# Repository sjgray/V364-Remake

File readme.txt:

Commodore V364 Prototype Remake Project   Steve J. Gray
=======================================

This is a project to remake the V364 prototype computer from Commodore.
This would have been the flagship model in the TED/264 series, and
would feature a larger case with numeric keypad and built-in speech
synthesis using a more integrated version of the Magic Voice ("MV")
cartridge that was released for the C64.

This project will involve several different tasks:

 1) Create a PCB that matches the existing prototype layout as close as possible.
 2) Create a functional equivalent to the custom speech gate array chip.
 3) Create an MX switch compatible keyboard with numeric pad OR just the numeric
    pad that can be used with a standard Plus/4 keyboard.
 4) Create cherry MX keycaps.
 5) Create 3D modelled cursor arrow keys and function keys.
 6) Create a 3D modelled case of the V364 case to match the V364 motherboard
 7) Create a 3D modelled case that will accept a Plus/4 motherboard and keyboard
    for those just wanting the look. Use addon numeric keypad.
 8) Create a speech cartridge for existing 264-series computers.
 9) Create an internal Speech development board for 264-series.
10) Create replica case badge.
11) Clone the C64 MV to confirm schematics and as a base for other variations.

Status Overview  **** This project is not complete!!!! ****
---------------

The following have been posted even if not complete:

* 3D case for Plus/4 motherboard. In progress. Has not been printed.
* Complete "full" keyboard. Uses standard MX switches. Tested working. May need updating.
* Separate Numeric Pad. Supports standard and low-profile MX switches. Untested.
* Complete Custom Cherry MX keycaps. Tested ok.
* Preliminary Motherboard PCB. Most components are in place. No routing.
* C64 Magic Voice clone. Mostly done.

Keyboard
--------

A mechanical keyboard PCB has been produced with numeric pad. Custom cherry keycaps
were ordered from Maxkeyboard.com. These were tested on a real Plus/4 computer and
are working. A standalone MX numeric keypad PCB will be created for those wanting to
use a Plus/4 keyboard (feasibility to be determined).

Numeric Keypad
---------------

This has not been tested! Use at own risk. The original "full" V364 keyboard was
loaded and everything but the numeric pad and one connecter were retained so there
should be no reason the numpad would not work, however it may require modifications
depending on the final case design.

The V364 motherboard should have an extra keyboard connector to connect
both a Plus/4 keyboard and this numeric pad. For Plus/4 motherboards it
will need a 2-to-1 adapter board to connect both.

I have ordered PCBs and will build one with low-profile switches to confirm operation.

Keycaps
-------

Keycaps have been completed for the normal cherry type keys. The non-standard
function keys and arrow cursor keys have not been started. These will have to wait
for the 3D case to be completed.

Keycap Labels
-------------

 Custom colour printed keycaps were made by Maxkeyboard.com. A SVG file was submitted
in order to make the dyesub printed keycaps. This SVG file can also be used to make water-slide or vinyl sheet for using on blank keycaps.

Case
----

Initially I took 2 Plus/4 cases and modded them to resemble a V364 case. Of course
the function key area was wrong but it allowed me to test a Plus/4 motherboard and
the MX keyboard. The Plus/4 keyboard ribbon connector was replaced with a normal
pin header (like the C64) for testing.

A 3D replica case is being designed using the free version of Sketchup. It is mostly
complete but has not been printed. Final design will depend on the motherboard PCB
design to match port locations and mounting holes etc.

Badge
-----

I want to duplicate the real V364 badge. This was done in the same style as the Plus/4
badge. It uses raised silver logo, letters, and model# as well as the same multi-coloured
rainbow stripes. I think this will have to be done with separate printed components.
The base can be made of plastic with colour-laser printed sticker applied over top. The
rest will need to be resin-printed in order to get the proper detail and spray-painted
silver. Each will need to be glued on top of the sticker sheet. Currently only the silver
parts have been 3D modelled.

Motherboard PCB
---------------

A replica PCB is in progress using Kicad. The board dimensions and layout are mostly
done by underlaying a photo of a real V364 motherboard for alignment. The Plus/4 schematic was used as a base and the speech section was derived by work done by
Bo Zimmerman and Richard Atkinson. The Magic Voice schematic was used to obtain the
Toshiba T6721 chip pinout and audio output circuit.

Custom Gate Array
-----------------

This has not started. Since the V364 has been emulated it should be possible to
duplicate the functionality on some type of programmable logic chip and turned into
a pin-compatible plug-in board.

Speech Cartridge
----------------

This is a cartridge based on the V364 speech circuitry. It consists of just the speech chips
with an audio output jack. It will also need a connection to the "F0" pin on the PLA inside
the computer.

Speech Dev Board
-----------------

This is a development board to add speech internally using either the MV chipset or the
custom V364 Gate Array (recreated in FPGA etc). The MV circuit was simplified for the 264.
It connects via ribbon cable to one ROM socket on the computer motherboard and has several
flyouts to connect various places.

The ROM from the computer is transferred to this board. The V364 ROM/EPROM is installed in
the other socket and the Toshiba T6721A in it's socket.

* If you are using the MV set: install the 6525 and LA05 chips.
* If you have the V364 Gate Array recreation just install that only.

C64 Magic Voice replica
-----------------------

This is a replica of the C64 Magic Voice cartridge. This will verify that existing schematics
of the Magic Voice are correct and then we can use this as the basis for 264-series versions
if the custom gate array can not be cloned. The schematic was entered into Kicad and a board
was created, along with creating a Magic Voice gate array symbol. The design is mostly completed,
with layout and components closely matching the original except for a few minor changes to
some traces due to Kicad's trace constraints, and also the RCA connectors could not
be found so a modern version was substituted.

Project notes
-------------

I will release work-in-progress for anyone interested in following along. Anyone that
wishes to help is encouraged to contact me.

Steve

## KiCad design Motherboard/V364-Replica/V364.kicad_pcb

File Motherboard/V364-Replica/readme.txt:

Commodore V364 Prototype Remake Project   Steve J. Gray
=======================================

This is a project to remake the V364 prototype computer from Commodore.
This would have been the flagship model in the TED/264 series, and
would feature a larger case with numeric keypad and built-in speech
synthesis using a more integrated version of the Magic Voice cartridge
that was released for the C64.

Motherboard PCB
---------------

A replica PCB is in progress using Kicad. The board dimensions and layout are mostly
done by underlaying a photo of a real V364 motherboard for alignment. The Plus/4 schematic was used as a base and the speech section was derived by work done by
Bo Zimmerman and Richard Atkinson. The Magic Voice schematic was used to obtain the
Toshiba T6721 chip pinout and audio output circuit.

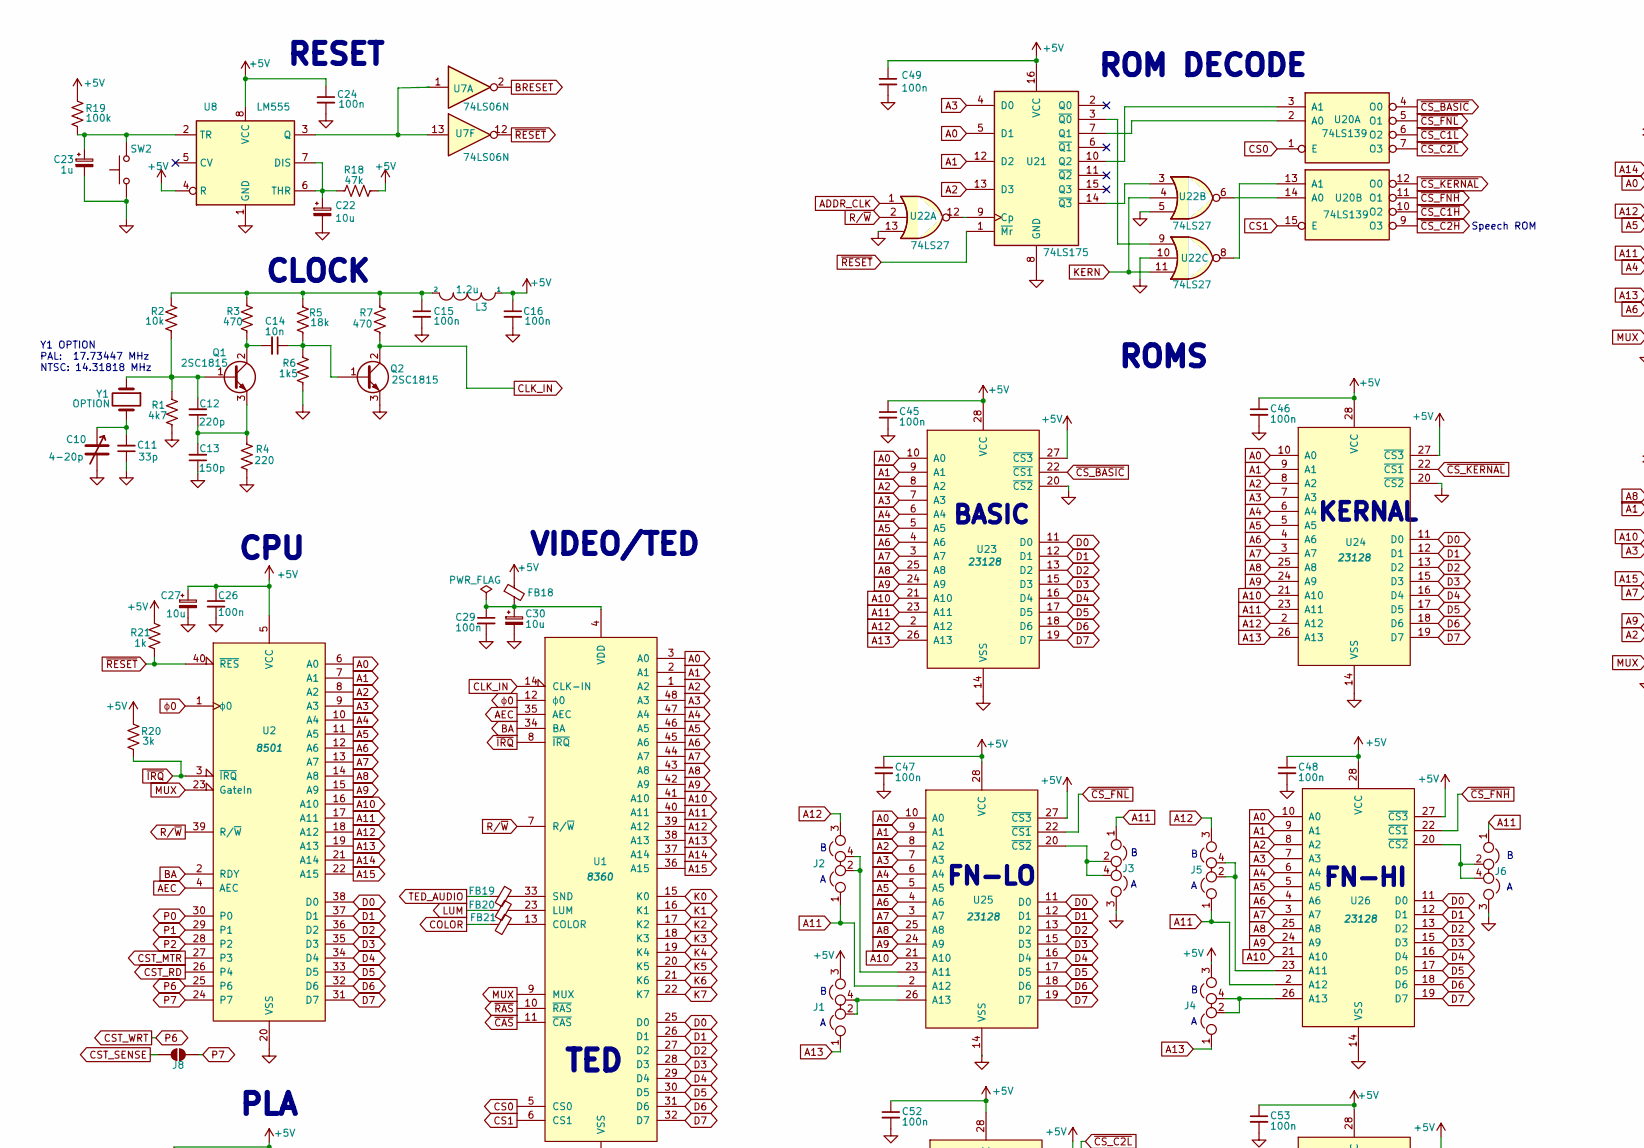
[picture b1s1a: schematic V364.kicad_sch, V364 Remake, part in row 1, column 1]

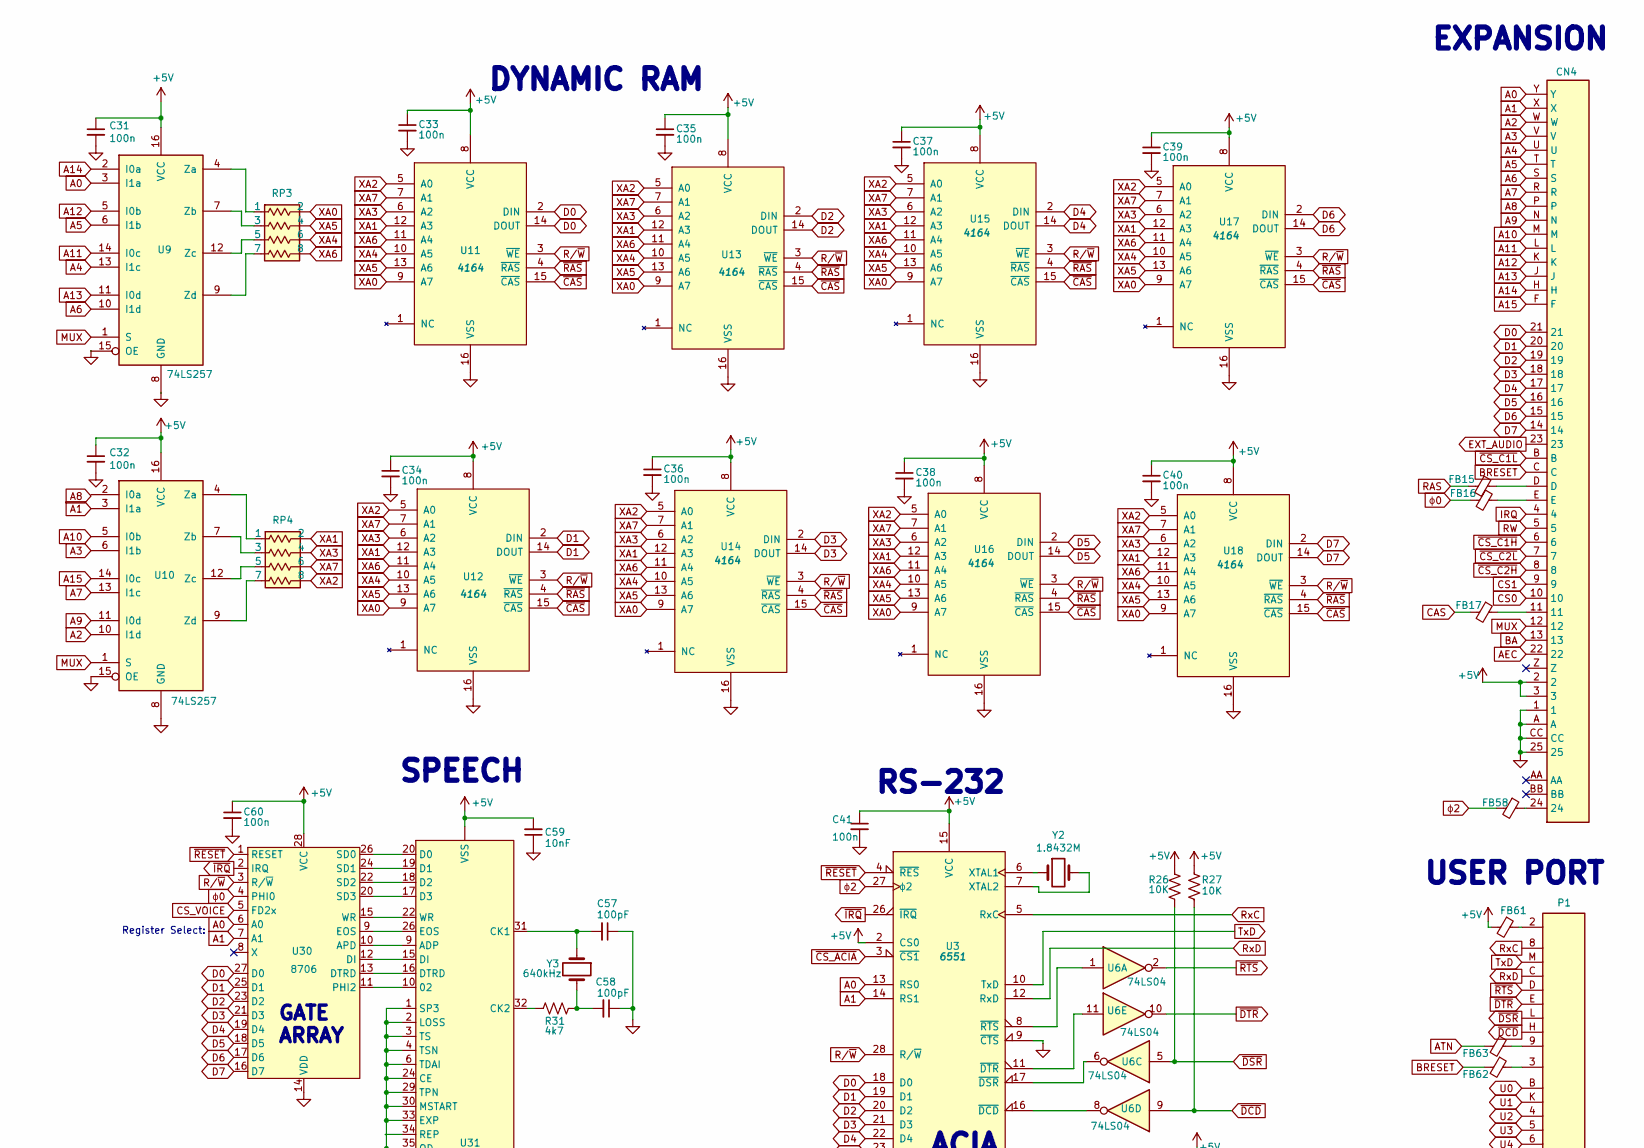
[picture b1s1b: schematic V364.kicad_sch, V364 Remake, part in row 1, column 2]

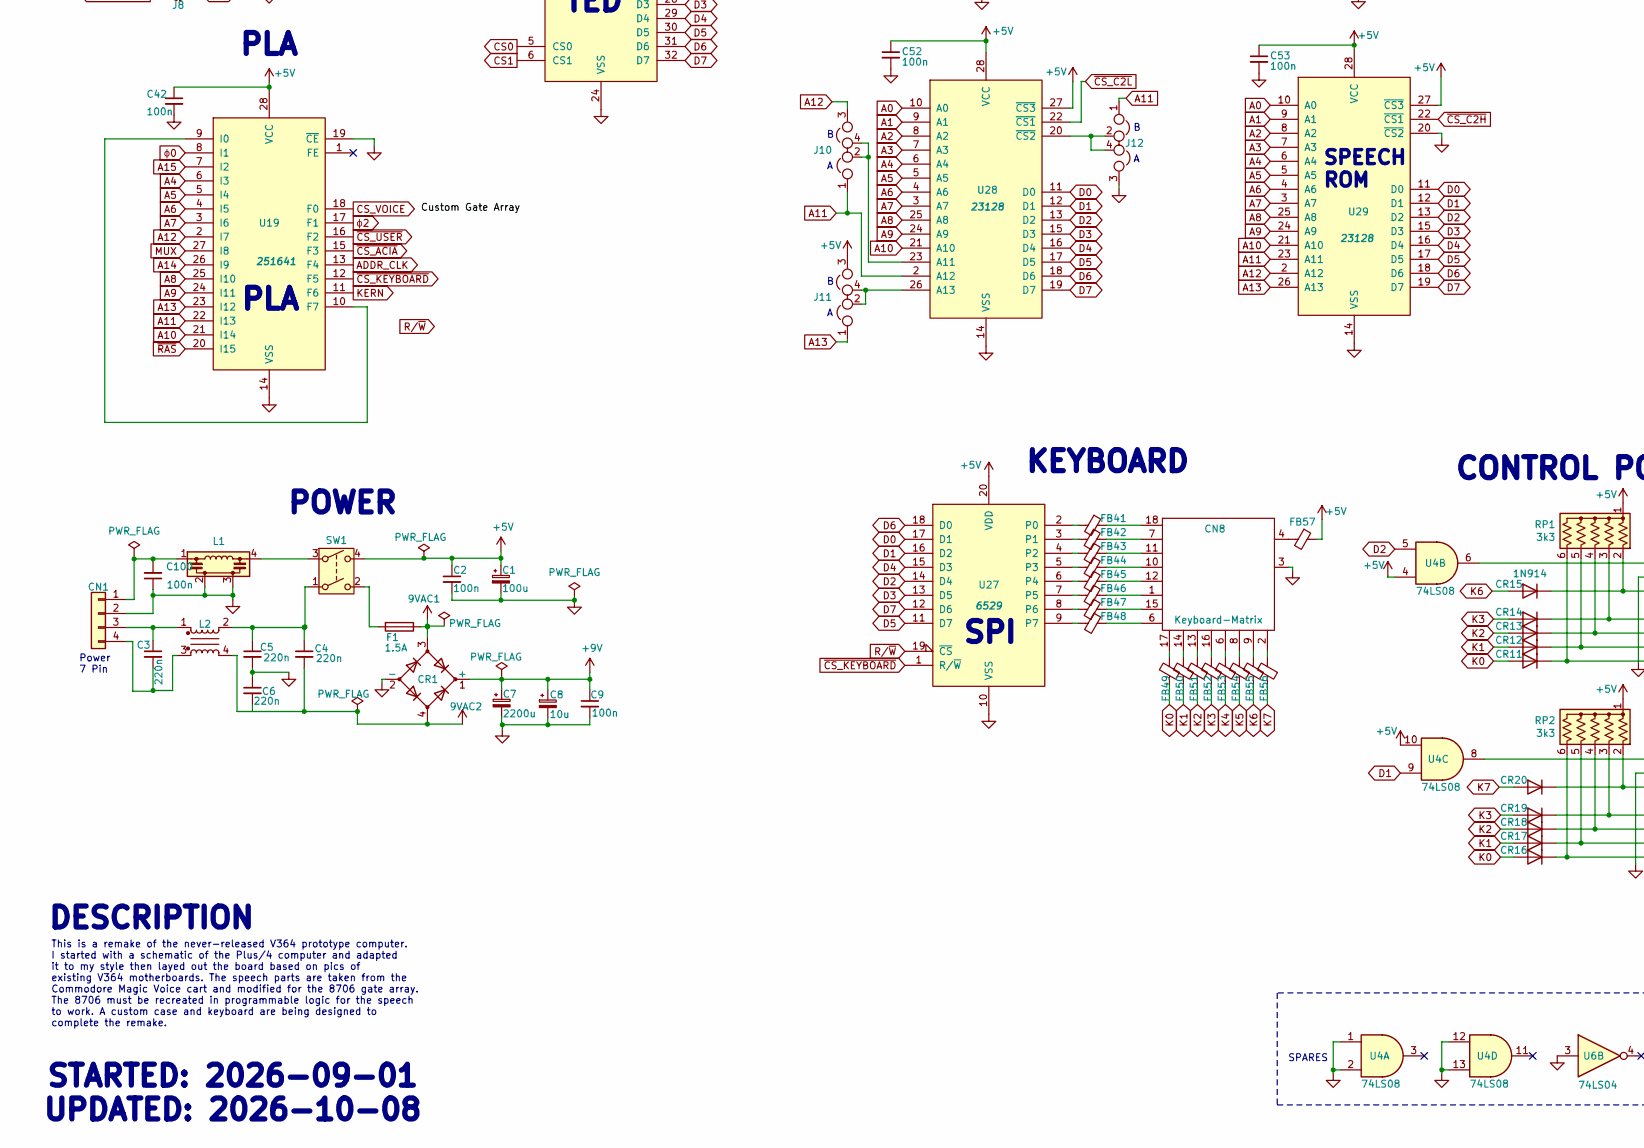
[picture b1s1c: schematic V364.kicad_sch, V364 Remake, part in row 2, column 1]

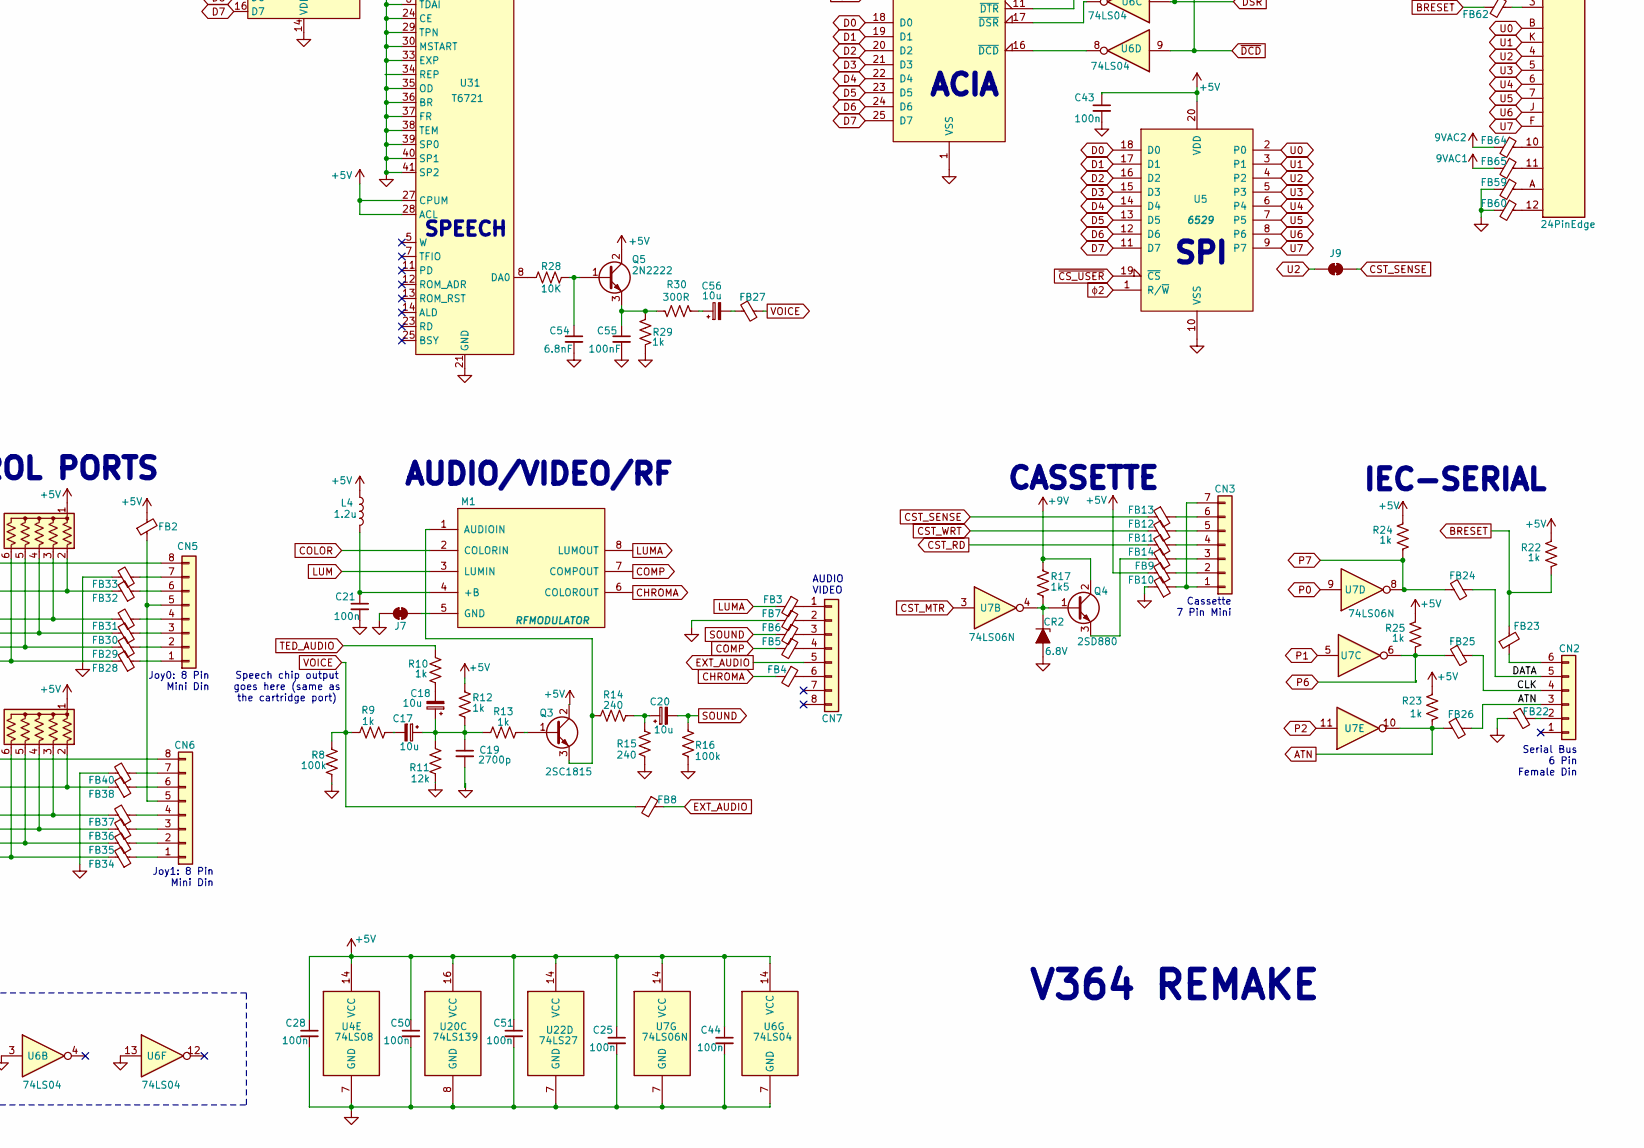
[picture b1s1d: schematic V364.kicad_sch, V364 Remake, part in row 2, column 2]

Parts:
C1: 100u; CP_Radial_D8.0mm_P3.50mm
C2, C9, C15, C16, C21, C24, C25, C26, C28, C29, C31, C32, C33, C34, C35, C36, C37, C38, C39, C40, C41, C42, C43, C44, C45, C46, C47, C48, C49, C50, C51, C52, C53, C60: 100n; C_Disc_D5.0mm_W2.5mm_P5.00mm
C3: 220n; C_Disc_D12.5mm_W5.0mm_P10.00mm
C4: 220n; Capacitor_D12.5mm_W5.0mm_P10.00mm
C5, C6: 220n; C_Disc_D5.0mm_W2.5mm_P5.00mm
C7: 2200u; CP_Axial_L40.0mm_D16.0mm_P48.00mm_Horizontal
C8, C20: 10u; CP_Radial_D6.3mm_P2.50mm
C10: 4-20p; TrimCap_251029-02
C11: 33p; C_Disc_D5.0mm_W2.5mm_P5.00mm
C12: 220p; C_Disc_D5.0mm_W2.5mm_P5.00mm
C13: 150p; C_Disc_D5.0mm_W2.5mm_P5.00mm
C14: 10n; C_Disc_D5.0mm_W2.5mm_P5.00mm
C17, C18, C22, C27, C30, C56: 10u; C_Disc_D5.0mm_W2.5mm_P5.00mm
C19: 2700p; C_Disc_D5.0mm_W2.5mm_P5.00mm
C23: 1u; CP_Radial_D6.3mm_P2.50mm
C54: 6.8nF; C_Disc_D12.5mm_W5.0mm_P10.00mm
C55: 100nF; C_Disc_D12.5mm_W5.0mm_P10.00mm
C57, C58: 100pF; C_Disc_D5.0mm_W2.5mm_P5.00mm
C59: 10nF; C_Disc_D5.0mm_W2.5mm_P5.00mm
C100: 100n; C_Disc_D4.7mm_W2.5mm_P5.00mm
CN1: Conn_01x04; Connector_Power_4pin_251614_01
CN2: Conn_01x07; Connector_DIN_Female_6Pin_3rows
CN3: Conn_01x07; Connector_Mini-DIN_Female_7Pin_2rows
CN4: 50PinEdge; 50Pin_Edge_Connector
CN5, CN6: Conn_01x08; Connector_Mini-DIN_Female_8Pin_2rows
CN7: Conn_01x08; Connector_DIN_Female_8Pin_3rows
CN8: Keyboard-Matrix; Keyboard_Connector
CR1: D_Bridge_+-AA; Diode_Bridge_12.5x12.5
CR2: 6.8V; D_A-405_P12.70mm_Horizontal
CR11, CR12, CR13, CR14, CR15, CR16, CR17, CR18, CR19, CR20: 1N914; D_DO-35_SOD27_P12.70mm_Horizontal
F1: 1.5A; Fuseholder_Cylinder-6.3x32mm
FB2, FB3, FB4, FB5, FB6, FB7, FB8, FB9, FB10, FB11, FB12, FB13, FB14, FB15, FB16, FB17, FB18, FB19, FB20, FB21, FB22, FB23, FB24, FB25, FB26, FB27, FB28, FB29, FB30, FB31, FB32, FB33, FB34, FB35, FB36, FB37, FB38, FB40, FB41, FB42, FB43, FB44, FB45, FB46, FB47, FB48, FB49, FB50, FB51, FB52, FB53, FB54, FB55, FB56, FB57, FB58, FB59, FB60, FB61, FB62, FB63, FB64, FB65: Ferrite_Bead_Small; Ferrite_Bead_L5.0mm_D3.6mm_P13.00mm_Horizontal
J1, J2, J3, J4, J5, J6, J10, J11, J12: Jumper_NC_Dual; Jumper
J7, J9: SolderJumper_2_Bridged; SolderJumper-2_P1.3mm_Bridged_RoundedPad1.0x1.5mm
J8: SolderJumper_2_Open; SolderJumper-2_P1.3mm_Open_RoundedPad1.0x1.5mm
L1: EMI_Filter; EMI-Filter
L2: EMI_Filter_CommonMode; Noise_Filter
L3, L4: 1.2u; L_Axial_L10.0mm_D4.0mm_P15.5mm_Horizontal
M1: RFMODULATOR; RF_Modulator
P1: 24PinEdge; 24Pin_Edge
Q1, Q2, Q3: 2SC1815; TO-92L_Inline_Wide
Q4: 2SD880; TO-220-3_Vertical
Q5: 2N2222; TO-220-3_Vertical
R1, R31: 4k7; Resistor_Horizontal
R2: 10k; Resistor_Horizontal
R3, R7: 470; Resistor_Horizontal
R4: 220; Resistor_Horizontal
R5: 18k; Resistor_Horizontal
R6, R17: 1k5; Resistor_Horizontal
R8, R16, R19: 100k; Resistor_Horizontal
R9, R10, R12, R13, R21, R22, R23, R24, R25, R29: 1k; Resistor_Horizontal
R11: 12k; Resistor_Horizontal
R14, R15: 240; Resistor_Horizontal
R18: 47k; Resistor_Horizontal
R20: 3k; Resistor_Horizontal
R26, R27, R28: 10K; Resistor_Horizontal
R30: 300R; Resistor_Horizontal
RP1, RP2: 3k3; R_Array_SIP6
RP3, RP4: Resistor-Network; R_Array_SIP8
SW1: SW_DPST; Switch-Rocker
SW2: SW_Push; Switch-Pushbutton
U1: 8360; DIP-48_W15.24mm
U2: 8501; DIP-40_W15.24mm
U3: 6551; DIP-28_W15.24mm
U4: 74LS08; DIP-14_W7.62mm
U5, U27: 6529; DIP-20_W7.62mm
U6: 74LS04; DIP-14_W7.62mm
U7: 74LS06N; DIP-14_W7.62mm
U8: LM555; DIP-8_W7.62mm
U9, U10: 74LS257; DIP-16_W7.62mm
U11, U12, U13, U14, U15, U16, U17, U18: 4164; DIP-16_W7.62mm
U19: 251641; DIP-28_W15.24mm
U20: 74LS139; DIP-16_W7.62mm
U21: 74LS175; DIP-16_W7.62mm
U22: 74LS27; DIP-14_W7.62mm
U23, U24, U25, U26, U28, U29: 23128; DIP-28_W15.24mm
U30: 8706; DIP-28_W15.24mm_LongPads
U31: T6721; DIP-42_W15.24mm_Socket_LongPads
Y1: OPTION; Crystal_HC18-U_Horizontal
Y2: 1.8432M; Crystal_HC33-U_Horizontal
Y3: 640kHz; Crystal_HC18-U_Vertical

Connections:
9VAC1: CR1.3, F1.1, FB65.2
9VAC2: C4.2, C6.2, CR1.4, FB64.2, L2.4
+5V: C1.1, C2.1, C16.1, C24.1, C25.1, C26.1, C27.1, C28.1, C31.1, C32.1, C33.1, C34.1, C35.1, C36.1, C37.1, C38.1, C39.1, C40.1, C41.1, C42.1, C43.1, C44.1, C45.1, C46.1, C47.1, C48.1, C49.1, C50.1, C51.1, C52.1, C53.1, C59.2, C60.1, CN4.2, CN4.3, FB2.2, FB9.1, FB18.1, FB57.1, FB61.2, J1.3, J4.3, J11.3, L3.1, L4.1, Q3.2 (C), Q5.2 (C), R12.1, R18.1, R19.2, R20.1, R21.2, R22.1, R23.1, R24.1, R25.1, R26.1, R27.1, RP1.1 (common), RP2.1 (common), SW1.4, U2.5 (VCC), U3.2 (CS0), U3.15 (VCC), U4.4, U4.10, U4.14 (VCC), U5.20 (VDD), U6.14 (VCC), U7.14 (VCC), U8.4 (R), U8.8 (VCC), U9.16 (VCC), U10.16 (VCC), U11.8 (VCC), U12.8 (VCC), U13.8 (VCC), U14.8 (VCC), U15.8 (VCC), U16.8 (VCC), U17.8 (VCC), U18.8 (VCC), U19.28 (VCC), U20.16 (VCC), U21.16 (VCC), U22.14 (VCC), U23.27 (~CS3), U23.28 (VCC), U24.27 (~CS3), U24.28 (VCC), U25.27 (~CS3), U25.28 (VCC), U26.27 (~CS3), U26.28 (VCC), U27.20 (VDD), U28.27 (~CS3), U28.28 (VCC), U29.27 (~CS3), U29.28 (VCC), U30.28 (VCC), U31. (VSS), U31.27 (CPUM), U31.28 (ACL)
+9V: C7.1, C8.1, C9.1, CR1.1 (+), Q4.2 (C), R17.1
/CLK: CN2.4, FB25.2
/DATA: CN2.5, FB24.2
A0: CN4.Y, U1.3 (A0), U2.6 (A0), U3.13 (RS0), U9.3 (I1a), U21.5 (D1), U23.10 (A0), U24.10 (A0), U25.10 (A0), U26.10 (A0), U28.10 (A0), U29.10 (A0), U30.6 (A0)
A1: CN4.X, U1.2 (A1), U2.7 (A1), U3.14 (RS1), U10.3 (I1a), U21.12 (D2), U23.9 (A1), U24.9 (A1), U25.9 (A1), U26.9 (A1), U28.9 (A1), U29.9 (A1), U30.7 (A1)
A2: CN4.W, U1.1 (A2), U2.8 (A2), U10.10 (I1d), U21.13 (D3), U23.8 (A2), U24.8 (A2), U25.8 (A2), U26.8 (A2), U28.8 (A2), U29.8 (A2)
A3: CN4.V, U1.48 (A3), U2.9 (A3), U10.6 (I1b), U21.4 (D0), U23.7 (A3), U24.7 (A3), U25.7 (A3), U26.7 (A3), U28.7 (A3), U29.7 (A3)
A4: CN4.U, U1.47 (A4), U2.10 (A4), U9.13 (I1c), U19.6 (I3), U23.6 (A4), U24.6 (A4), U25.6 (A4), U26.6 (A4), U28.6 (A4), U29.6 (A4)
A5: CN4.T, U1.46 (A5), U2.11 (A5), U9.6 (I1b), U19.5 (I4), U23.5 (A5), U24.5 (A5), U25.5 (A5), U26.5 (A5), U28.5 (A5), U29.5 (A5)
A6: CN4.S, U1.45 (A6), U2.12 (A6), U9.10 (I1d), U19.4 (I5), U23.4 (A6), U24.4 (A6), U25.4 (A6), U26.4 (A6), U28.4 (A6), U29.4 (A6)
A7: CN4.R, U1.44 (A7), U2.13 (A7), U10.13 (I1c), U19.3 (I6), U23.3 (A7), U24.3 (A7), U25.3 (A7), U26.3 (A7), U28.3 (A7), U29.3 (A7)
A8: CN4.P, U1.43 (A8), U2.14 (A8), U19.25 (I10), U23.25 (A8), U24.25 (A8), U25.25 (A8), U26.25 (A8), U28.25 (A8), U29.25 (A8)
A9: CN4.N, U1.42 (A9), U2.15 (A9), U10.11 (I0d), U19.24 (I11), U23.24 (A9), U24.24 (A9), U25.24 (A9), U26.24 (A9), U28.24 (A9), U29.24 (A9)
A10: CN4.M, U1.41 (A10), U2.16 (A10), U10.5 (I0b), U19.21 (I14), U23.21 (A10), U24.21 (A10), U25.21 (A10), U26.21 (A10), U28.21 (A10), U29.21 (A10)
A11: CN4.L, J2.1, J3.1, J5.1, J6.1, J10.1, J12.1, U1.40 (A11), U2.17 (A11), U9.14 (I0c), U19.22 (I13), U23.23 (A11), U24.23 (A11), U25.2 (A12), U26.2 (A12), U28.2 (A12), U29.23 (A11)
A12: CN4.K, J2.3, J5.3, J10.3, U1.39 (A12), U2.18 (A12), U9.5 (I0b), U19.2 (I7), U23.2 (A12), U24.2 (A12), U29.2 (A12)
A13: CN4.J, J1.1, J4.1, J11.1, U1.38 (A13), U2.19 (A13), U9.11 (I0d), U19.23 (I12), U23.26 (A13), U24.26 (A13), U29.26 (A13)
A14: CN4.H, U1.37 (A14), U2.21 (A14), U9.2 (I0a), U19.26 (I9)
A15: CN4.F, U1.36 (A15), U2.22 (A15), U10.14 (I0c), U19.7 (I2)
ADDR_CLK: U19.13 (F4), U22.1
AEC: CN4.22, U1.35 (AEC), U2.4 (AEC)
ATN: CN2.3, FB26.1, FB26.2, FB63.2, R23.2, U7.10
BA: CN4.13, U1.34 (BA), U2.2 (RDY)
BRESET: CN4.C, FB23.2, FB62.2, R22.2, U7.2
CAS: FB17.2
CLK_IN: Q2.2 (C), R7.2, U1.14 (CLK-IN)
COLOR: FB21.2, M1.2 (COLORIN)
CS0: CN4.10, U1.5 (CS0), U20.1 (E)
CS1: CN4.9, U1.6 (CS1), U20.15 (E)
CST_MTR: U2.27 (P3), U7.3
CST_RD: FB11.1, U2.26 (P4)
CST_SENSE: FB13.1, J8.1 (A), J9.2 (B)
CST_WRT: FB12.1, FB25.1, R25.2, U2.25 (P6), U7.6
D0: CN4.21, U1.25 (D0), U2.38 (D0), U3.18 (D0), U5.18 (D0), U11.2 (DIN), U11.14 (DOUT), U23.11 (D0), U24.11 (D0), U25.11 (D0), U26.11 (D0), U27.17 (D1), U28.11 (D0), U29.11 (D0), U30.27 (D0)
D1: CN4.20, U1.26 (D1), U2.37 (D1), U3.19 (D1), U4.9, U5.17 (D1), U12.2 (DIN), U12.14 (DOUT), U23.12 (D1), U24.12 (D1), U25.12 (D1), U26.12 (D1), U27.16 (D2), U28.12 (D1), U29.12 (D1), U30.25 (D1)
D2: CN4.19, U1.27 (D2), U2.36 (D2), U3.20 (D2), U4.5, U5.16 (D2), U13.2 (DIN), U13.14 (DOUT), U23.13 (D2), U24.13 (D2), U25.13 (D2), U26.13 (D2), U27.14 (D4), U28.13 (D2), U29.13 (D2), U30.23 (D2)
D3: CN4.18, U1.28 (D3), U2.35 (D3), U3.21 (D3), U5.15 (D3), U14.2 (DIN), U14.14 (DOUT), U23.15 (D3), U24.15 (D3), U25.15 (D3), U26.15 (D3), U27.13 (D5), U28.15 (D3), U29.15 (D3), U30.21 (D3)
D4: CN4.17, U1.29 (D4), U2.34 (D4), U3.22 (D4), U5.14 (D4), U15.2 (DIN), U15.14 (DOUT), U23.16 (D4), U24.16 (D4), U25.16 (D4), U26.16 (D4), U27.15 (D3), U28.16 (D4), U29.16 (D4), U30.19 (D4)
D5: CN4.16, U1.30 (D5), U2.33 (D5), U3.23 (D5), U5.13 (D5), U16.2 (DIN), U16.14 (DOUT), U23.17 (D5), U24.17 (D5), U25.17 (D5), U26.17 (D5), U27.11 (D7), U28.17 (D5), U29.17 (D5), U30.18 (D5)
D6: CN4.15, U1.31 (D6), U2.32 (D6), U3.24 (D6), U5.12 (D6), U17.2 (DIN), U17.14 (DOUT), U23.18 (D6), U24.18 (D6), U25.18 (D6), U26.18 (D6), U27.18 (D0), U28.18 (D6), U29.18 (D6), U30.17 (D6)
D7: CN4.14, U1.32 (D7), U2.31 (D7), U3.25 (D7), U5.11 (D7), U18.2 (DIN), U18.14 (DOUT), U23.19 (D7), U24.19 (D7), U25.19 (D7), U26.19 (D7), U27.12 (D6), U28.19 (D7), U29.19 (D7), U30.16 (D7)
GND: C1.2, C2.2, C5.2, C6.1, C7.2, C8.2, C9.2, C10.2, C11.1, C13.1, C15.2, C16.2, C19.2, C21.2, C22.2, C23.2, C24.2, C25.2, C26.2, C27.2, C28.2, C29.2, C30.2, C31.2, C32.2, C33.2, C34.2, C35.2, C36.2, C37.2, C38.2, C39.2, C40.2, C41.2, C42.2, C43.2, C44.2, C45.2, C46.2, C47.2, C48.2, C49.2, C50.2, C51.2, C52.2, C53.2, C54.2, C55.2, C57.1, C58.1, C59.1, C60.2, C100.1, CN1.2, CN4.1, CN4.25, CN4.A, CN4.CC, CN8.3, CR1.2 (-), CR2.2 (A), FB7.2, FB10.2, FB22.1, FB33.2, FB40.2, FB59.2, FB60.2, J3.3, J6.3, J7.1 (A), J12.3, L1.2, L1.3, Q2.3 (E), R1.2, R4.2, R6.2, R8.2, R11.2, R15.2, R16.2, R29.2, SW2.1, U1.24 (VSS), U2.20 (VSS), U3.1 (VSS), U3.9 (~CTS), U4.1, U4.2, U4.7 (GND), U4.12, U4.13, U5.10 (VSS), U6.3, U6.7 (GND), U6.13, U7.7 (GND), U8.1 (GND), U9.8 (GND), U9.15 (OE), U10.8 (GND), U10.15 (OE), U11.16 (VSS), U12.16 (VSS), U13.16 (VSS), U14.16 (VSS), U15.16 (VSS), U16.16 (VSS), U17.16 (VSS), U18.16 (VSS), U19.14 (VSS), U19.19 (~CE), U20.8 (GND), U21.8 (GND), U22.5, U22.7 (GND), U22.10, U22.13, U23.14 (VSS), U23.20 (~CS2), U24.14 (VSS), U24.20 (~CS2), U25.14 (VSS), U26.14 (VSS), U27.10 (VSS), U28.14 (VSS), U29.14 (VSS), U29.20 (~CS2), U30.14 (VDD), U31.1 (SP3), U31.2 (LOSS), U31.3 (TS), U31.4 (TSN), U31.6 (TDAI), U31.21 (GND), U31.24 (CE), U31.29 (TPN), U31.30 (MSTART), U31.33 (EXP), U31.35 (OD), U31.36 (BR), U31.37 (FR), U31.38 (TEM), U31.39 (SP0), U31.40 (SP1), U31.41 (SP2)
IRQ: CN4.4
K0: CR11.2 (A), CR16.2 (A), FB49.1, U1.15 (K0)
K1: CR12.2 (A), CR17.2 (A), FB50.1, U1.16 (K1)
K2: CR13.2 (A), CR18.2 (A), FB51.1, U1.17 (K2)
K3: CR14.2 (A), CR19.2 (A), FB52.1, U1.18 (K3)
K4: FB53.1, U1.19 (K4)
K5: FB54.1, U1.20 (K5)
K6: CR15.2 (A), FB55.1, U1.21 (K6)
K7: CR20.2 (A), FB56.1, U1.22 (K7)
KERN: U19.11 (F6), U22.4, U22.11
LUM: FB20.2, M1.3 (LUMIN)
MUX: CN4.12, U1.9 (MUX), U2.23 (GateIn), U9.1 (S), U10.1 (S), U19.27 (I8)
unnamed: C4.1, C5.1, L2.2, SW1.1
unnamed: C10.1, C11.2, Y1.2
unnamed: C15.1, L3.2, R2.1, R3.1, R5.1, R7.1
unnamed: C17.1, C18.1, C19.1, R11.1, R12.2, R13.2
unnamed: C17.2, R9.1
unnamed: C18.2, R10.2
unnamed: C20.1, R14.1, R15.1
unnamed: C20.2, FB6.2, R16.1
unnamed: C56.1, R30.2
unnamed: C56.2, FB27.1
unnamed: C58.2, R31.2, Y3.2
unnamed: C100.2, CN1.1, L1.1
unnamed: C3.1, CN1.3, L2.1
unnamed: C3.2, CN1.4, L2.3
unnamed: CN2.2, FB22.2
unnamed: CN2.6, FB23.1
unnamed: CN3.1, CN3.7, FB10.1
unnamed: CN3.2, FB9.2
unnamed: CN3.3, FB14.2
unnamed: CN3.4, FB11.2
unnamed: CN3.5, FB12.2
unnamed: CN3.6, FB13.2
unnamed: CN4.11, FB17.1
unnamed: CN4.24, FB58.1
unnamed: CN4.D, FB15.1
unnamed: CN4.E, FB16.1
unnamed: CN5.1, FB28.1
unnamed: CN5.2, FB29.1
unnamed: CN5.3, FB30.1
unnamed: CN5.4, FB31.1
unnamed: CN5.5, CN6.5, FB2.1
unnamed: CN5.6, FB32.1
unnamed: CN5.7, FB33.1
unnamed: CN5.8, U4.6
unnamed: CN6.1, FB34.1
unnamed: CN6.2, FB35.1
unnamed: CN6.3, FB36.1
unnamed: CN6.4, FB37.1
unnamed: CN6.6, FB38.1
unnamed: CN6.7, FB40.1
unnamed: CN6.8, U4.8
unnamed: CN7.1, FB3.1
unnamed: CN7.2, FB7.1
unnamed: CN7.3, FB6.1
unnamed: CN7.4, FB5.1
unnamed: CN7.6, FB4.1
unnamed: CN8.1, FB46.2
unnamed: CN8.2, FB56.2
unnamed: CN8.4, FB57.2
unnamed: CN8.7, FB42.2
unnamed: CN8.8, FB54.2
unnamed: CN8.9, FB55.2
unnamed: CN8.10, FB44.2
unnamed: CN8.11, FB43.2
unnamed: CN8.12, FB45.2
unnamed: CN8.13, FB51.2
unnamed: CN8.14, FB50.2
unnamed: CN8.15, FB47.2
unnamed: CN8.16, FB52.2
unnamed: CN8.17, FB49.2
unnamed: CN8.18, FB41.1
unnamed: CR2.1 (K), Q4.1 (B), R17.2, U7.4
unnamed: CR11.1 (K), FB28.2, RP1.6 (R5)
unnamed: CR12.1 (K), FB29.2, RP1.5 (R4)
unnamed: CR13.1 (K), FB30.2, RP1.4 (R3)
unnamed: CR14.1 (K), FB31.2, RP1.3 (R2)
unnamed: CR15.1 (K), FB32.2, RP1.2 (R1)
unnamed: CR16.1 (K), FB34.2, RP2.6 (R5)
unnamed: CR17.1 (K), FB35.2, RP2.5 (R4)
unnamed: CR18.1 (K), FB36.2, RP2.4 (R3)
unnamed: CR19.1 (K), FB37.2, RP2.3 (R2)
unnamed: CR20.1 (K), FB38.2, RP2.2 (R1)
unnamed: F1.2, SW1.2
unnamed: FB59.1, P1.A
unnamed: FB60.1, P1.12
unnamed: FB61.1, P1.2
unnamed: FB62.1, P1.3
unnamed: FB63.1, P1.9
unnamed: FB64.1, P1.10
unnamed: FB65.1, P1.11
unnamed: J7.2 (B), M1.5 (GND)
unnamed: L1.4, SW1.3
unnamed: C21.1, L4.2, M1.4 (+B)
unnamed: M1.1 (AUDIOIN), Q3.3 (E), R14.2
unnamed: FB4.2, M1.6 (COLOROUT)
unnamed: FB5.2, M1.7 (COMPOUT)
unnamed: FB3.2, M1.8 (LUMOUT)
unnamed: C12.2, Q1.1 (B), R1.1, R2.2, Y1.1
unnamed: C14.2, Q1.2 (C), R3.2
unnamed: C12.1, C13.2, Q1.3 (E), R4.1
unnamed: C14.1, Q2.1 (B), R5.2, R6.1
unnamed: Q3.1 (B), R13.1
unnamed: FB14.1, Q4.3 (E)
unnamed: C54.1, Q5.1 (B), R28.1
unnamed: C55.1, Q5.3 (E), R29.1, R30.1
unnamed: FB21.1, U1.13 (COLOR)
unnamed: FB20.1, U1.23 (LUM)
unnamed: FB19.1, U1.33 (SND)
unnamed: C29.1, C30.1, FB18.2, U1.4 (VDD)
unnamed: U3.6 (XTAL1), Y2.1
unnamed: U3.7 (XTAL2), Y2.2
unnamed: U3.16 (~DCD), U6.8
unnamed: U3.17 (~DSR), U6.6
unnamed: U3.11 (~DTR), U6.11
unnamed: U3.8 (~RTS), U6.1
unnamed: C22.1, R18.2, U8.6 (THR), U8.7 (DIS)
unnamed: U7.1, U7.13, U8.3 (Q)
unnamed: C23.1, R19.1, SW2.2, U8.2 (TR)
unnamed: RP3.1, U9.4 (Za)
unnamed: RP3.3, U9.7 (Zb)
unnamed: RP3.5, U9.12 (Zc)
unnamed: RP3.7, U9.9 (Zd)
unnamed: RP4.1, U10.4 (Za)
unnamed: RP4.3, U10.7 (Zb)
unnamed: RP4.5, U10.12 (Zc)
unnamed: RP4.7, U10.9 (Zd)
unnamed: U19.9 (I0), U19.10 (F7)
unnamed: U20.2 (A0), U21.7 (Q1)
unnamed: U20.3 (A1), U21.10 (Q2)
unnamed: U20.14 (A0), U22.6
unnamed: U20.13 (A1), U22.8
unnamed: U21.9 (Cp), U22.12
unnamed: U21.3 (~Q0), U22.9
unnamed: U21.14 (~Q3), U22.3
unnamed: J2.2, J2.4, U25.23 (A11)
unnamed: J1.2, J1.4, U25.26 (A13)
unnamed: J3.2, J3.4, U25.20 (~CS2)
unnamed: J5.2, J5.4, U26.23 (A11)
unnamed: J4.2, J4.4, U26.26 (A13)
unnamed: J6.2, J6.4, U26.20 (~CS2)
unnamed: FB41.2, U27.2 (P0)
unnamed: FB42.1, U27.3 (P1)
unnamed: FB43.1, U27.4 (P2)
unnamed: FB44.1, U27.5 (P3)
unnamed: FB45.1, U27.6 (P4)
unnamed: FB46.1, U27.7 (P5)
unnamed: FB47.1, U27.8 (P6)
unnamed: FB48.2, U27.9 (P7)
unnamed: J10.2, J10.4, U28.23 (A11)
unnamed: J11.2, J11.4, U28.26 (A13)
unnamed: J12.2, J12.4, U28.20 (~CS2)
unnamed: U30.10 (APD), U31.9 (ADP)
unnamed: U30.12 (DI), U31.15 (DI)
unnamed: U30.13 (DTRD), U31.16 (DTRD)
unnamed: U30.9 (EOS), U31.26 (EOS)
unnamed: U30.11 (PHI2), U31.10 (02)
unnamed: U30.26 (SD0), U31.20 (D0)
unnamed: U30.24 (SD1), U31.19 (D1)
unnamed: U30.22 (SD2), U31.18 (D2)
unnamed: U30.20 (SD3), U31.17 (D3)
unnamed: U30.15 (WR), U31.22 (WR)
unnamed: C57.2, U31.31 (CK1), Y3.1
unnamed: R31.1, U31.32 (CK2)
unnamed: R28.2, U31.8 (DA0)
P0: U2.30 (P0), U7.9
P1: U2.29 (P1), U7.5
P2: U2.28 (P2), U7.11
P7: FB24.1, J8.2 (B), R24.2, U2.24 (P7), U7.8
RAS: FB15.2
RW: CN4.5
RxC: P1.8, U3.5 (RxC)
RxD: P1.C, U3.12 (RxD)
R/~W: U1.7 (R/~W), U2.39 (R/~W), U3.28 (R/~W), U11.3 (~WE), U12.3 (~WE), U13.3 (~WE), U14.3 (~WE), U15.3 (~WE), U16.3 (~WE), U17.3 (~WE), U18.3 (~WE), U22.2, U27.19 (~CS), U30.3 (R/~W)
TED_AUDIO: FB19.2, R10.1
TxD: P1.M, U3.10 (TxD)
U0: P1.B, U5.2 (P0)
U1: P1.K, U5.3 (P1)
U2: J9.1 (A), P1.4, U5.4 (P2)
U3: P1.5, U5.5 (P3)
U4: P1.6, U5.6 (P4)
U5: P1.7, U5.7 (P5)
U6: P1.J, U5.8 (P6)
U7: P1.F, U5.9 (P7)
XA0: RP3.2, U11.9 (A7), U12.9 (A7), U13.9 (A7), U14.9 (A7), U15.9 (A7), U16.9 (A7), U17.9 (A7), U18.9 (A7)
XA1: RP4.2, U11.12 (A3), U12.12 (A3), U13.12 (A3), U14.12 (A3), U15.12 (A3), U16.12 (A3), U17.12 (A3), U18.12 (A3)
XA2: RP4.8, U11.5 (A0), U12.5 (A0), U13.5 (A0), U14.5 (A0), U15.5 (A0), U16.5 (A0), U17.5 (A0), U18.5 (A0)
XA3: RP4.4, U11.6 (A2), U12.6 (A2), U13.6 (A2), U14.6 (A2), U15.6 (A2), U16.6 (A2), U17.6 (A2), U18.6 (A2)
XA4: RP3.6, U11.10 (A5), U12.10 (A5), U13.10 (A5), U14.10 (A5), U15.10 (A5), U16.10 (A5), U17.10 (A5), U18.10 (A5)
XA5: RP3.4, U11.13 (A6), U12.13 (A6), U13.13 (A6), U14.13 (A6), U15.13 (A6), U16.13 (A6), U17.13 (A6), U18.13 (A6)
XA6: RP3.8, U11.11 (A4), U12.11 (A4), U13.11 (A4), U14.11 (A4), U15.11 (A4), U16.11 (A4), U17.11 (A4), U18.11 (A4)
XA7: RP4.6, U11.7 (A1), U12.7 (A1), U13.7 (A1), U14.7 (A1), U15.7 (A1), U16.7 (A1), U17.7 (A1), U18.7 (A1)
~CAS: U1.11 (~CAS), U11.15 (~CAS), U12.15 (~CAS), U13.15 (~CAS), U14.15 (~CAS), U15.15 (~CAS), U16.15 (~CAS), U17.15 (~CAS), U18.15 (~CAS)
~CS_ACIA: U3.3 (~CS1), U19.15 (F3)
~CS_BASIC: U20.4 (O0), U23.22 (~CS1)
~CS_C1H: CN4.6, U20.10 (O2)
~CS_C1L: CN4.B, U20.6 (O2)
~CS_C2L: CN4.7, U20.7 (O3), U28.22 (~CS1)
~CS_FNH: U20.11 (O1), U26.22 (~CS1)
~CS_FNL: U20.5 (O1), U25.22 (~CS1)
~CS_KERNAL: U20.12 (O0), U24.22 (~CS1)
~CS_KEYBOARD: U19.12 (F5), U27.1 (R/~W)
~CS_USER: U5.19 (~CS), U19.16 (F2)
~DCD: P1.H, R27.2, U6.9
~DSR: P1.L, R26.2, U6.5
~DTR: P1.E, U6.10
~IRQ: R20.2, U1.8 (~IRQ), U2.3 (~IRQ), U3.26 (~IRQ), U30.2 (IRQ)
~RAS: U1.10 (~RAS), U11.4 (~RAS), U12.4 (~RAS), U13.4 (~RAS), U14.4 (~RAS), U15.4 (~RAS), U16.4 (~RAS), U17.4 (~RAS), U18.4 (~RAS), U19.20 (I15)
~RESET: R21.1, U2.40 (~RES), U3.4 (~RES), U7.12, U21.1 (~Mr), U30.1 (RESET)
~RTS: P1.D, U6.2
ϕ0: FB16.2, U1.12 (ϕ0), U2.1 (ϕ0), U19.8 (I1), U30.4 (PHI0)
ϕ2: FB58.2, U3.27 (ϕ2), U5.1 (R/~W), U19.17 (F1)

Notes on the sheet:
CLOCK
USER PORT
KERNAL
PLA
CPU
This is a remake of the never-released V364 prototype computer. I started with a schematic of the Plus/4 computer and adapted it to my style then layed out the board based on pics of existing V364 motherboards. The speech parts are taken from the Commodore Magic Voice cart and modified for the 8706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
EXPANSION
SPI
Speech ROM
RS-232
RESET
ROMS
ROM DECODE
KEYBOARD
SPEECH ROM
Joy1: 8 Pin Mini Din
CONTROL PORTS
STARTED: 2026-09-01 UPDATED: 2026-10-08
Serial Bus 6 Pin Female Din
V364 REMAKE
Power 7 Pin
TED
DESCRIPTION
BASIC
POWER
VIDEO/TED
Cassette 7 Pin Mini
AUDIO/VIDEO/RF
FN-LO
SPEECH
SPARES
DYNAMIC RAM
GATE ARRAY
ACIA
IEC-SERIAL
Joy0: 8 Pin Mini Din
Y1 OPTION PAL: 17.73447 MHz NTSC: 14.31818 MHz
Speech chip output goes here (same as the cartridge port)
AUDIO VIDEO
CASSETTE

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
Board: 2 copper layers, 239 parts (0 on the bottom side), 259 nets, no tracks yet.
